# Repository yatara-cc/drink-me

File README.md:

# Drink Me

4% ergo macropad

> However, this bottle was not marked ‘poison,’ so Alice ventured to taste it... ‘What a curious feeling!’ said Alice; ‘I must be shutting up like a telescope.’

## Getting started

### Hardware

-   The base and case are “snap-fit”; you can open and close them by pushing or pulling vertically with care.
-   Make sure switch pins are completely straight before inserting them into the hotswap sockets, otherwise the pins may miss the holes and cause damage.
-   It is recommended to remove the case from the base/thumbrest and support the hotswap sockets with your finger or thumb while inserting switches.

### Firmware

Drink Me ships with [VIA](https://caniusevia.com/) firmware preinstalled. To customise your keymap, install and run the [latest version](https://github.com/the-via/releases) on your computer; when you plug in your Drink Me it will be recognised and you can edit the keymap in realtime.

You can also use the online [QMK Configurator](https://config.qmk.fm/#/yatara/drink_me/LAYOUT) to create a custom firmware for your Drink Me. Alternatively download the [QMK](https://github.com/qmk/qmk_firmware) source where you will find [example code and keymaps for Drink Me](https://github.com/qmk/qmk_firmware/tree/master/keyboards/yatara/drink_me) that can be modified to use any of QMK's [extensive features](https://docs.qmk.fm/#/).

### Help & Support

Buyers can access personalised support by sending a message to the email address on the PayPal invoice.

Realtime support may also be available on [Discord](https://discord.gg/yeXgVFX).

## Production

You can use the files in the Releases section of this repository to manufacture the PCB and printed parts.

### PCB

PCBs can be produced by submitting the Gerber files to a PCB manufacturer and requesting a 1.6mm thick PCB.

The PCBs for the official group by were manufactured by [JLCPCB](https://jlcpcb.com/) and the PCB designs are tailored for their service.

#### Bill of Materials

The following components (or equivalent) are also required for the PCB:

-   1 x ATMEGA32U2-AUR
-   1 x 16MHz 18P Crystal 
-   4 x Kailh MX Hotswap Sockets - available from [KBDFans](https://kbdfans.com/)
-   1 x Reset Switch SPST-NO 0.05A 12V
-   1 x 4.7µF 0805 Capacitor
-   1 x 1.0µF 0805 Capacitor
-   2 x 0.1µF 0805 Capacitor
-   2 x 22pF 0805 Capacitor
-   2 x 5.1kΩ 0805 Resistor (for USB-C only)
-   2 x 10kΩ 0805 Resistor
-   2 x 22Ω 0805 Resistor
-   1 x 500mA 1206 Fuse
-   Plus one of the following, depending on the PCB USB socket selected:
    -   1 x Hirose USB2.0 Micro B SMD ZX62D-B-5PA8(30)
    -   1 x Hirose USB2.0 Mini B SMD UX60SC-MB-5S8(80)
    -   1 x Korean Hroparts USB Type C TYPE-C-31-M-12 - available from [LCSC](https://lcsc.com/)
-   4 x MX-compatible switch modules - available from many sources
-   4 x MX-compatible keycaps - available from many sources

Where not specifically indicated, these components are available from Digi-Key, and compatible BOM files are included in releases for these parts.

### Printed Parts

Four printed parts are available:

-   Case: the main part of the keyboard that holds the PCB and switches
    -   This piece requires support material enabled for FDM printing
-   Base: and integrated base, back and thumb-rest
-   Back: a clip-on back to protect the PCB from dust
-   Rest: a separate thumb-rest

The Base and Back are “snap-fit”; they require fine tolerances so it is recommended to experiement with the horizontal or XY offset in your G-code slicer to achieve the most accurate results.

## Modification and Development

This project is released under the GNU General Public License v3. You are encouraged to modify its content to meet your own requirements provided you respect the terms of the licence.

This repository includes automated scripts for various tasks. However, the PCB and geometry files can be modified in their respective software without recourse to these scripts.

### Dependencies for automated scripts

-   POSIX OS (eg. Linux or OSX)
-   Bash
-   Gnu Make
-   Python >= 3.7
-   Meshlab

Python modules:

-   GeoTK
-   Kiplot

To install Python modules run:

```
make install-python
```

### PCB

#### Dependencies

-   [KiCad](https://kicad-pcb.org/download/) >= 5.1

Components from the following libraries were used, but these are not required in order to use the PCB files.

-   [Yatara KiCad library](https://github.com/yatara-cc/kicad)
-   [TMK symbol library](https://github.com/tmk/kicad_lib_tmk)
-   [TMK footprint library](https://github.com/tmk/keyboard_parts.pretty )
-   [ai03 USB C libraries](https://github.com/ai03-2725/Type-C.pretty)

#### Export Gerber files for manufacture

```
make gerber
ll gerber
```

### Printed Parts

#### Dependencies

-   OpenSCAD

#### Export STL files for manufacture

```
make stl
ll stl
```

## References

-   [Photo Gallery](https://imgur.com/a/9XkbmKo) - 2020-01-24
-   [Geekhack Interest Check](https://geekhack.org/index.php?topic=104449.0) - 2020-01-29
-   [Geekhack Group Buy](https://geekhack.org/index.php?topic=104974.0) - 2020-03-04
-   [Reddit r/MechanicalKeyboards first look](https://www.reddit.com/r/MechanicalKeyboards/comments/eswx1z/drink_me/) - 2020-01-23
-   [Reddit r/MechanicalKeyboards Interest Check & Giveaway](https://www.reddit.com/r/MechanicalKeyboards/comments/evu429/ic_drink_me_4_ergo_interest_check_giveaway/) - 2020-02-19
-   [Reddit r/MechanicalKeyboard Group Buy announcement](https://www.reddit.com/r/MechanicalKeyboards/comments/f9hhyl/drink_me_group_buy_starts_march_5th_2020/) - 2020-03-05
-   [Reddit r/MechanicalKeyboard Group Buy](https://www.reddit.com/r/MechanicalKeyboards/comments/fe147m/drink_me_group_buy_is_live/) - 2020-03-05
-   [Reddit r/mechmarket Group Buy](https://www.reddit.com/r/mechmarket/comments/fe16nw/gb_drink_me_4_ergo_group_buy_is_live/) - 2020-03-05
-   [QMK page](https://github.com/qmk/qmk_firmware/tree/master/keyboards/yatara/drink_me)
-   [QMK Pull Request](https://github.com/qmk/qmk_firmware/pull/8039) - 2020-01-30
-   [QMK Configurator Pull Request](https://github.com/qmk/qmk_configurator/pull/648) - 2020-01-30
-   [VIA Pull Request](https://github.com/the-via/keyboards/pull/37) - 2020-01-31

> ‘It was much pleasanter at home,’ thought poor Alice, ‘when one wasn’t always growing larger and smaller... I almost wish I hadn’t gone down that rabbit-hole

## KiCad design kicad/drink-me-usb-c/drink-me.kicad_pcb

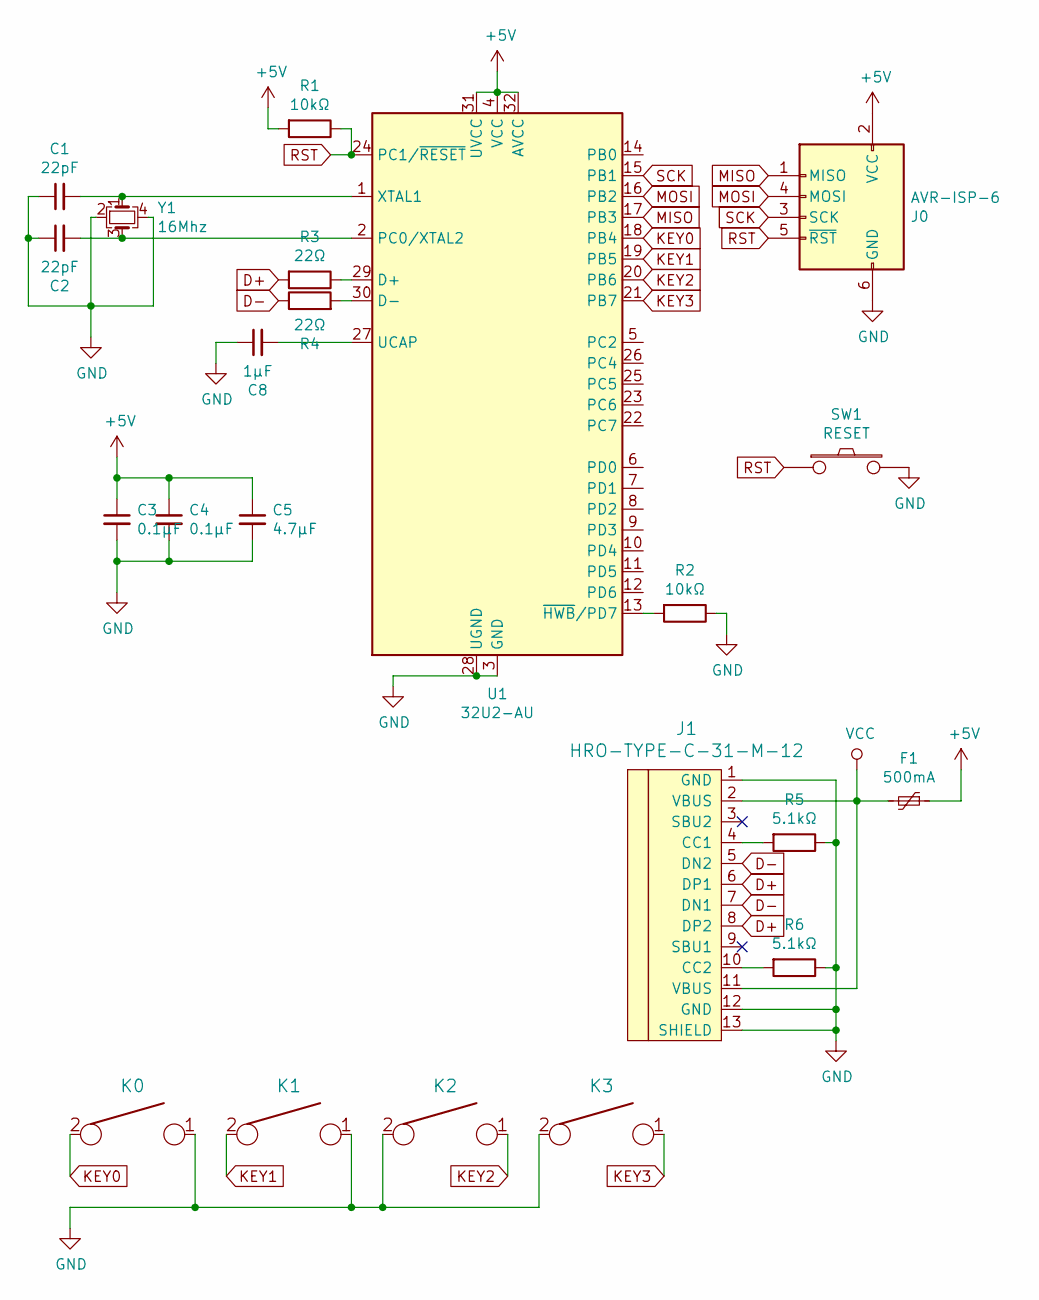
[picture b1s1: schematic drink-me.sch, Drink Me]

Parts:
C1, C2: 22pF; C_0805_2012Metric_Pad1.15x1.40mm_HandSolder
C3, C4: 0.1μF; C_0805_2012Metric_Pad1.15x1.40mm_HandSolder
C5: 4.7μF; C_0805_2012Metric_Pad1.15x1.40mm_HandSolder
C8: 1μF; C_0805_2012Metric_Pad1.15x1.40mm_HandSolder
F1: 500mA; Fuse_1206_3216Metric_Pad1.42x1.75mm_HandSolder
J0: AVR-ISP-6; PinHeader_2x03_P2.54mm_Vertical
J1: HRO-TYPE-C-31-M-12; HRO-TYPE-C-31-M-12-Assembly
K0, K1, K2, K3: KEYSW; Kailh_PCB_Socket_1511_MX
R1, R2: 10kΩ; R_0805_2012Metric_Pad1.15x1.40mm_HandSolder
R3, R4: 22Ω; R_0805_2012Metric_Pad1.15x1.40mm_HandSolder
R5, R6: 5.1kΩ; R_0805_2012Metric_Pad1.15x1.40mm_HandSolder
SW1: RESET; SW_SPST_TL3342
U1: 32U2-AU; TQFP-32_7x7mm_P0.8mm
Y1: 16Mhz; Crystal_SMD_3225-4Pin_3.2x2.5mm

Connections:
+5V: C3.1, C4.1, C5.1, F1.1, J0.2 (VCC), R1.2, U1.4 (VCC), U1.31 (UVCC), U1.32 (AVCC)
D+: J1.6 (DP1), J1.8 (DP2), R3.2
D-: J1.5 (DN2), J1.7 (DN1), R4.1
GND: C1.1, C2.1, C3.2, C4.2, C5.2, C8.1, J0.6 (GND), J1.1 (GND), J1.12 (GND), J1.13 (SHIELD), K0.1, K1.1, K2.2, K3.2, R2.1, R5.1, R6.1, SW1.2, U1.3 (GND), U1.28 (UGND), Y1.2, Y1.4
KEY0: K0.2, U1.18 (PB4)
KEY1: K1.2, U1.19 (PB5)
KEY2: K2.1, U1.20 (PB6)
KEY3: K3.1, U1.21 (PB7)
MISO: J0.1 (MISO), U1.17 (PB3)
MOSI: J0.4 (MOSI), U1.16 (PB2)
unnamed: C1.2, U1.1 (XTAL1), Y1.1
unnamed: C2.2, U1.2 (PC0/XTAL2), Y1.3
unnamed: C8.2, U1.27 (UCAP)
unnamed: J1.4 (CC1), R5.2
unnamed: J1.10 (CC2), R6.2
unnamed: R2.2, U1.13 (~HWB~/PD7)
unnamed: R3.1, U1.29 (D+)
unnamed: R4.2, U1.30 (D-)
RST: J0.5 (~RST), R1.1, SW1.1, U1.24 (PC1/~RESET)
SCK: J0.3 (SCK), U1.15 (PB1)
VCC: F1.2, J1.2 (VBUS), J1.11 (VBUS)

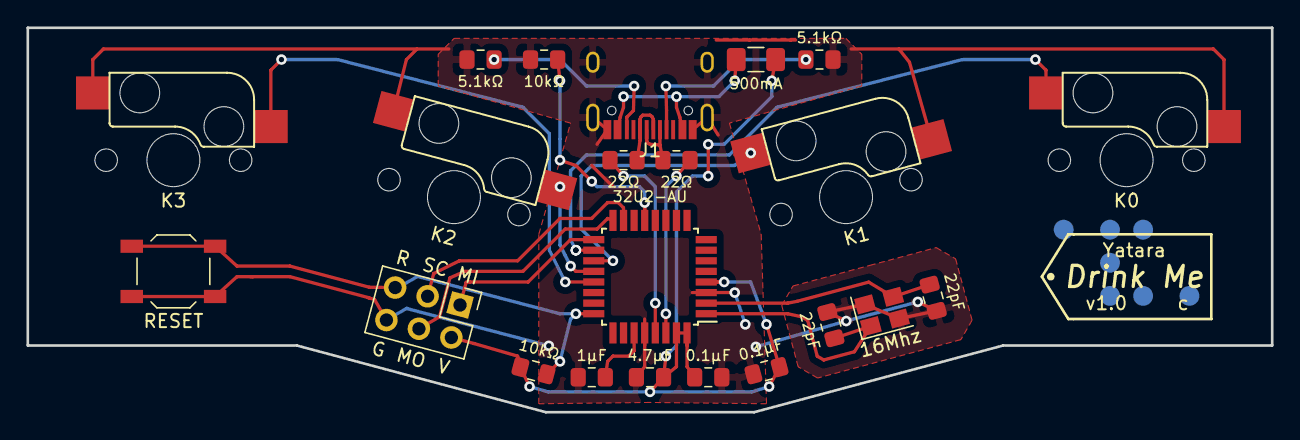
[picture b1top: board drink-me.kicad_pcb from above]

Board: 2 copper layers, 94.0 x 29.0 mm, 22 parts (0 on the bottom side), 21 nets.

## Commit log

2020-01-03 Initial commit.
2020-05-15 Add getting started instructions, hardware notes and references.
2020-05-15 Add USB-mini PCB and case, rest and base models for printing. Export scripts for Gerber and STL files. GNU GPLv3 licence.
2020-05-15 Add different KiCad projects for USB micro, USB mini, and USB type C. Add chiselled tip, chamfered rest, snap-fit clips and exploded scad view. Add KLE images and VIA keymap definition.
2020-05-20 Use HRO TYPE-C-31-M-12 USB-C connector. Add bill of materials. Add printed back part without rest, including tolerance adjustments.
2020-06-02 Add DXF plate file.
